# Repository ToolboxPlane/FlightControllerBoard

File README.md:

View this project on [CADLAB.io](https://cadlab.io/node/744). 

# FlightControllerBoard

A flight controller board for the mini Talon UAV based on a [STM32 Nucleo-32](http://www.st.com/content/st_com/en/products/evaluation-tools/product-evaluation-tools/mcu-eval-tools/stm32-mcu-eval-tools/stm32-mcu-nucleo/nucleo-l432kc.html).

Firmware availiable at [https://github.com/ToolboxBodensee/FlightController](https://github.com/ToolboxBodensee/FlightController).

## PCB

### Top layer

### Bottom Layer

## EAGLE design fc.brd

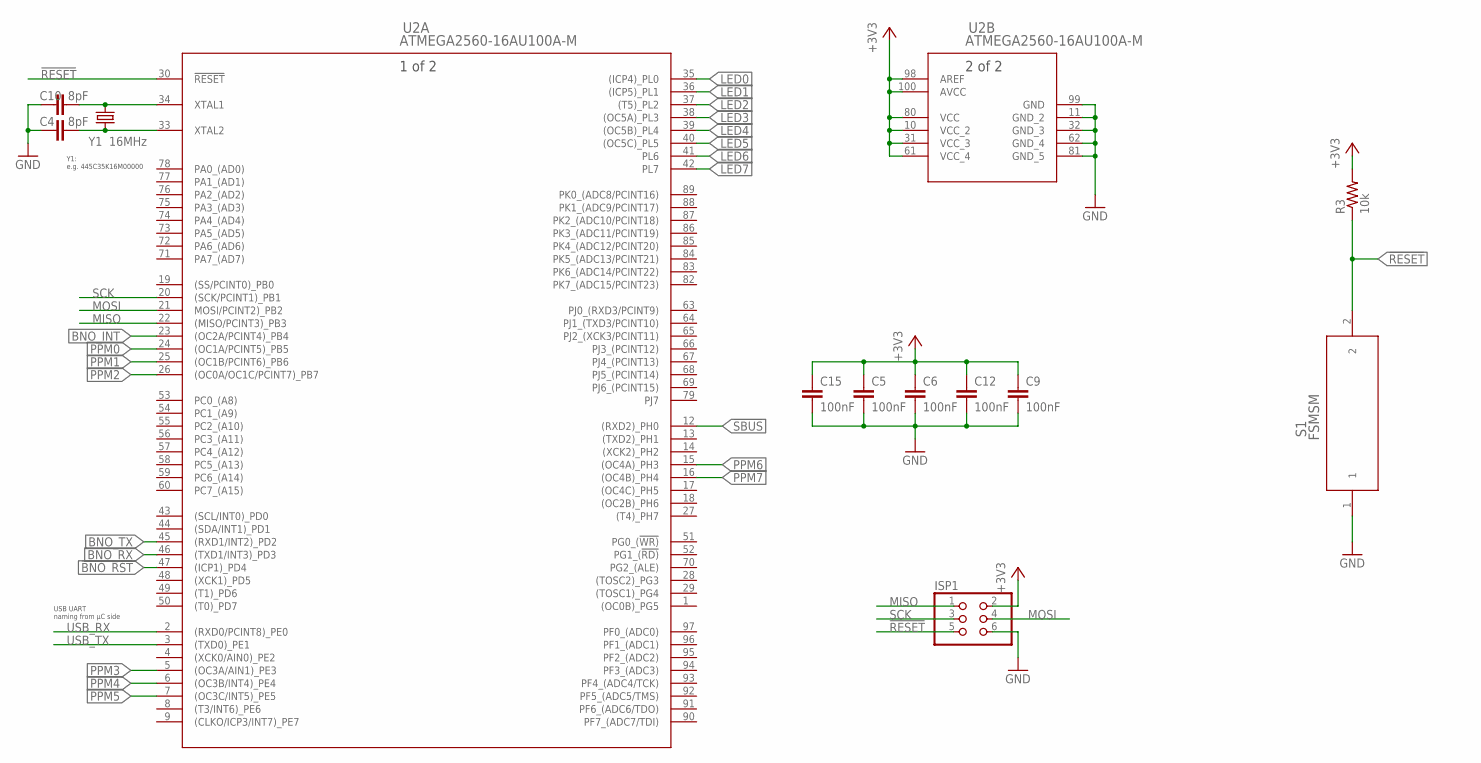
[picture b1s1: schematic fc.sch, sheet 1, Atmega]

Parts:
C4, C10: 8pF; 0603
C5, C6, C9, C12, C15: 100nF; 0603
ISP1: PINHD-2X3; 2X03
R3: 10k; 0603
S1: FSMSM; SWITCH_FSMSM
U2: ATMEGA2560-16AU100A-M; 100A-M
Y1: 16MHz; CRYSTAL-SMD-5X3.2-2PAD

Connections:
!BNO_RST: U2.47 ((ICP1)_PD4); also elsewhere on the board
!RESET: ISP1.5, R3.1, S1.2, U2.30 (!RESET)
!SBUS: U2.12 ((RXD2)_PH0); also elsewhere on the board
+3V3: C5.1, C6.1, C9.1, C12.1, C15.1, ISP1.2, R3.2, U2.10 (VCC_2), U2.31 (VCC_3), U2.61 (VCC_4), U2.80 (VCC), U2.98 (AREF), U2.100 (AVCC); also elsewhere on the board
BNO_INT: U2.23 ((OC2A/PCINT4)_PB4); also elsewhere on the board
BNO_RX: U2.46 ((TXD1/INT3)_PD3); also elsewhere on the board
BNO_TX: U2.45 ((RXD1/INT2)_PD2); also elsewhere on the board
GND: C4.1, C5.2, C6.2, C9.2, C10.1, C12.2, C15.2, ISP1.6, S1.1, U2.11 (GND_2), U2.32 (GND_3), U2.62 (GND_4), U2.81 (GND_5), U2.99 (GND); also elsewhere on the board
LED0: U2.35 ((ICP4)_PL0); also elsewhere on the board
LED1: U2.36 ((ICP5)_PL1); also elsewhere on the board
LED2: U2.37 ((T5)_PL2); also elsewhere on the board
LED3: U2.38 ((OC5A)_PL3); also elsewhere on the board
LED4: U2.39 ((OC5B)_PL4); also elsewhere on the board
LED5: U2.40 ((OC5C)_PL5); also elsewhere on the board
LED6: U2.41 (PL6); also elsewhere on the board
LED7: U2.42 (PL7); also elsewhere on the board
MISO: ISP1.1, U2.22 ((MISO/PCINT3)_PB3)
MOSI: ISP1.4, U2.21 (MOSI/PCINT2)_PB2)
unnamed: C10.2, U2.34 (XTAL1), Y1.P$2 (2)
unnamed: C4.2, U2.33 (XTAL2), Y1.P$1 (1)
PPM0: U2.24 ((OC1A/PCINT5)_PB5); also elsewhere on the board
PPM1: U2.25 ((OC1B/PCINT6)_PB6); also elsewhere on the board
PPM2: U2.26 ((OC0A/OC1C/PCINT7)_PB7); also elsewhere on the board
PPM3: U2.5 ((OC3A/AIN1)_PE3); also elsewhere on the board
PPM4: U2.6 ((OC3B/INT4)_PE4); also elsewhere on the board
PPM5: U2.7 ((OC3C/INT5)_PE5); also elsewhere on the board
PPM6: U2.15 ((OC4A)_PH3); also elsewhere on the board
PPM7: U2.16 ((OC4B)_PH4); also elsewhere on the board
SCK: ISP1.3, U2.20 ((SCK/PCINT1)_PB1)
USB_RX: U2.2 ((RXD0/PCINT8)_PE0); also elsewhere on the board
USB_TX: U2.3 ((TXD0)_PE1); also elsewhere on the board

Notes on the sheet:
Y1: e.g. 445C35K16M00000
USB UART naming from µC side

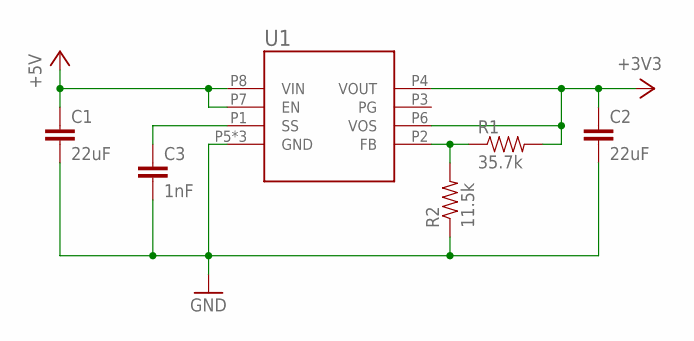
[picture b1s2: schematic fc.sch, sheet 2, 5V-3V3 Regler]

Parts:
C1, C2: 22uF; 0805
C3: 1nF; 0603
R1: 35.7k; 0603
R2: 11.5k; 0603
U1: LMZ21700; SIL0008E

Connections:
+3V3: C2.1, R1.2, U1.P4 (VOUT), U1.P6 (VOS); also elsewhere on the board
+5V: C1.1, U1.P7 (EN), U1.P8 (VIN); also elsewhere on the board
GND: C1.2, C2.2, C3.2, R2.1, U1.P5 (GND), U1.P9 (GND), U1.P10 (GND); also elsewhere on the board
unnamed: R1.1, R2.2, U1.P2 (FB)
unnamed: C3.1, U1.P1 (SS)

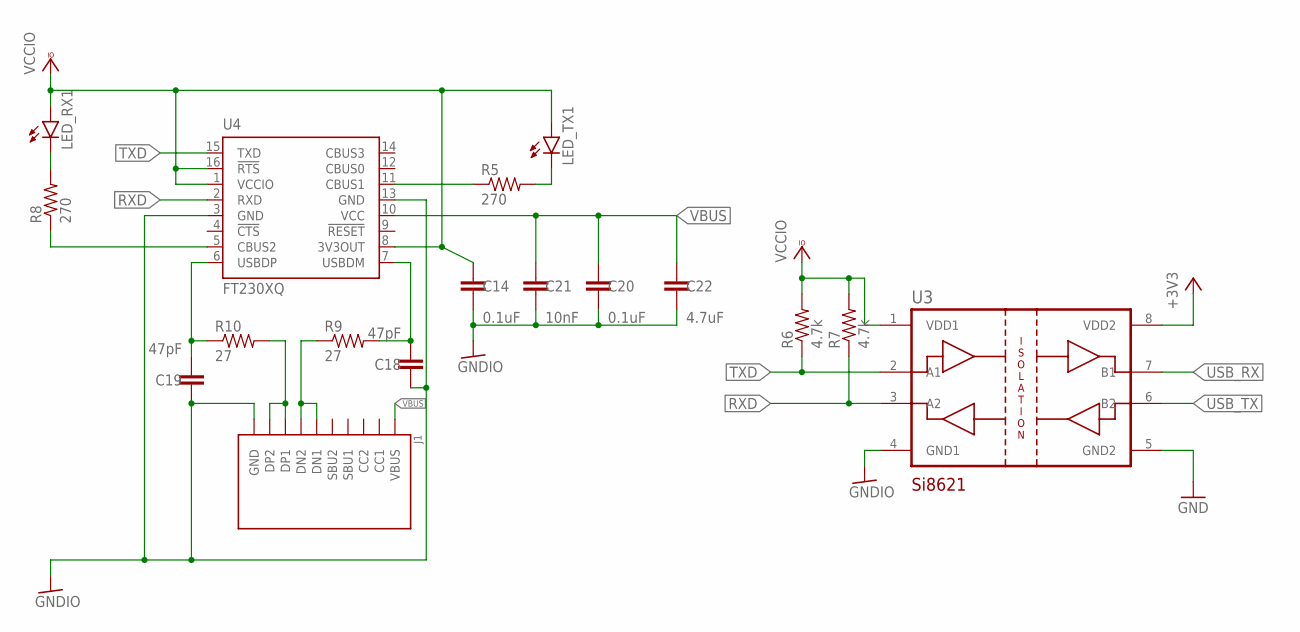
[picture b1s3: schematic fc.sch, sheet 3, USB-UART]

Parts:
C14, C20: 0.1uF; 0603
C18, C19: 47pF; 0603
C21: 10nF; 0603
C22: 4.7uF; 0603
J1: USBC
LED_RX1: LED0603; LED-0603
LED_TX1: LED0603; LED-0603
R5, R8: 270; 0603
R6, R7: 4.7k; 0603
R9, R10: 27; 0603
U3: SI8621AB-B-IS; SO08
U4: FT230XQ; QFN16

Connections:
+3V3: U3.8 (VDD2); also elsewhere on the board
D+1: J1.A6 (DP1), J1.B6 (DP2), R10.2
D-1: J1.A7 (DN1), J1.B7 (DN2), R9.1
GND: U3.5 (GND2); also elsewhere on the board
GNDIO: C14.2, C18.1, C19.1, C20.2, C21.2, C22.2, J1.A1 (GND), J1.A12 (GND), J1.S1 (GND), J1.S2 (GND), J1.S3 (GND), J1.S4 (GND), U3.4 (GND1), U4.3 (GND), U4.13 (GND)
unnamed: R5.1, U4.11 (CBUS1)
unnamed: LED_RX1.C, R8.2
unnamed: LED_TX1.C, R5.2
unnamed: R8.1, U4.5 (CBUS2)
RXD: R7.1, U3.3 (A2), U4.2 (RXD)
TXD: R6.1, U3.2 (A1), U4.15 (TXD)
USBDM1: C18.2, R9.2, U4.7 (USBDM)
USBDP1: C19.2, R10.1, U4.6 (USBDP)
USB_RX: U3.7 (B1); also elsewhere on the board
USB_TX: U3.6 (B2); also elsewhere on the board
VBUS: C20.1, C21.1, C22.1, J1.A4 (VBUS), J1.A9 (VBUS), U4.10 (VCC)
VCCIO: C14.1, LED_RX1.A, LED_TX1.A, R6.2, R7.2, U3.1 (VDD1), U4.1 (VCCIO), U4.8 (3V3OUT), U4.16 (!RTS)

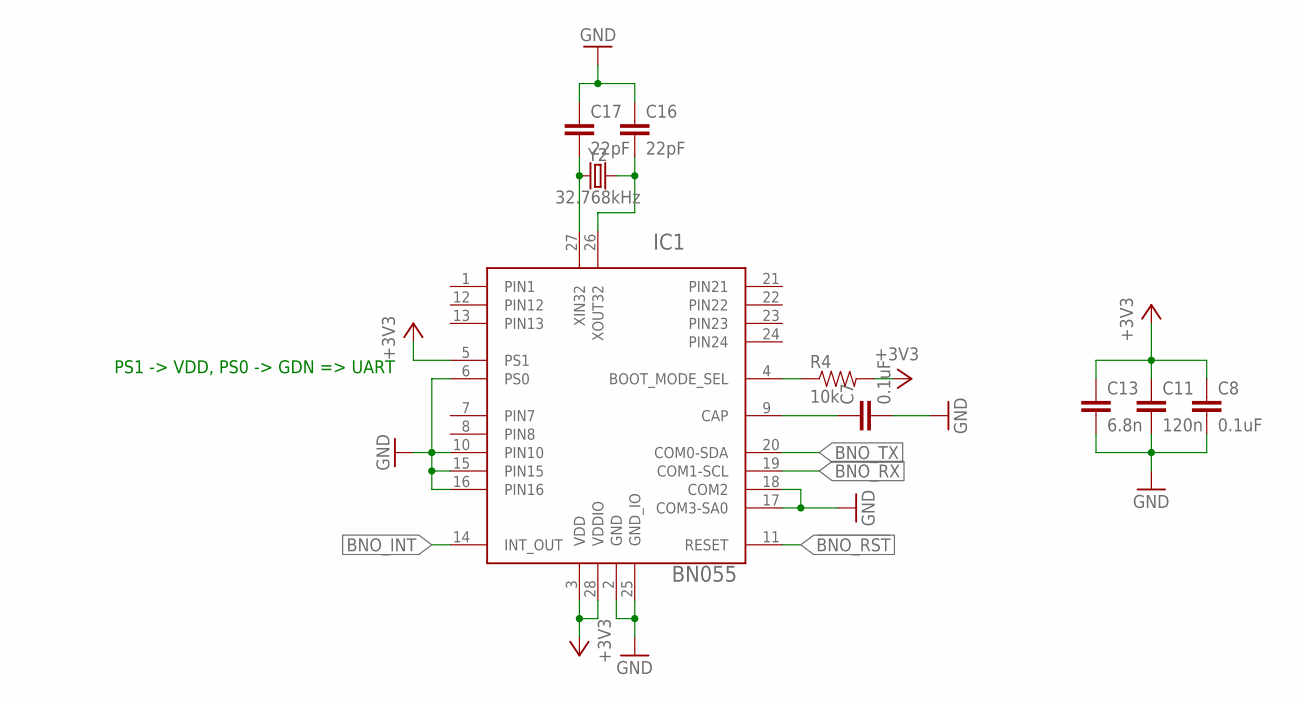
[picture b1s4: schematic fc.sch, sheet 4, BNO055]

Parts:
C7, C8: 0.1uF; 0603
C11: 120n; 0603
C13: 6.8n; 0603
C16, C17: 22pF; 0603
IC1: BN055; LGA-28_3.80X5.20/0.5
R4: 10k; 0603
Y2: 32.768kHz; CRYSTAL-SMD-3.2X1.5MM

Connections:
!BNO_RST: IC1.11 (RESET); also elsewhere on the board
+3V3: C8.1, C11.1, C13.1, IC1.3 (VDD), IC1.5 (PS1), IC1.28 (VDDIO), R4.2; also elsewhere on the board
BNO_INT: IC1.14 (INT_OUT); also elsewhere on the board
BNO_RX: IC1.19 (COM1-SCL); also elsewhere on the board
BNO_TX: IC1.20 (COM0-SDA); also elsewhere on the board
GND: C7.2, C8.2, C11.2, C13.2, C16.1, C17.1, IC1.2 (GND), IC1.6 (PS0), IC1.10 (PIN10), IC1.15 (PIN15), IC1.16 (PIN16), IC1.17 (COM3-SA0), IC1.18 (COM2), IC1.25 (GND_IO); also elsewhere on the board
unnamed: IC1.4 (BOOT_MODE_SEL), R4.1
unnamed: C7.1, IC1.9 (CAP)
unnamed: C17.2, IC1.27 (XIN32), Y2.P$1 (1)
unnamed: C16.2, IC1.26 (XOUT32), Y2.P$2 (2)

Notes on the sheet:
PS1 -> VDD, PS0 -> GDN => UART

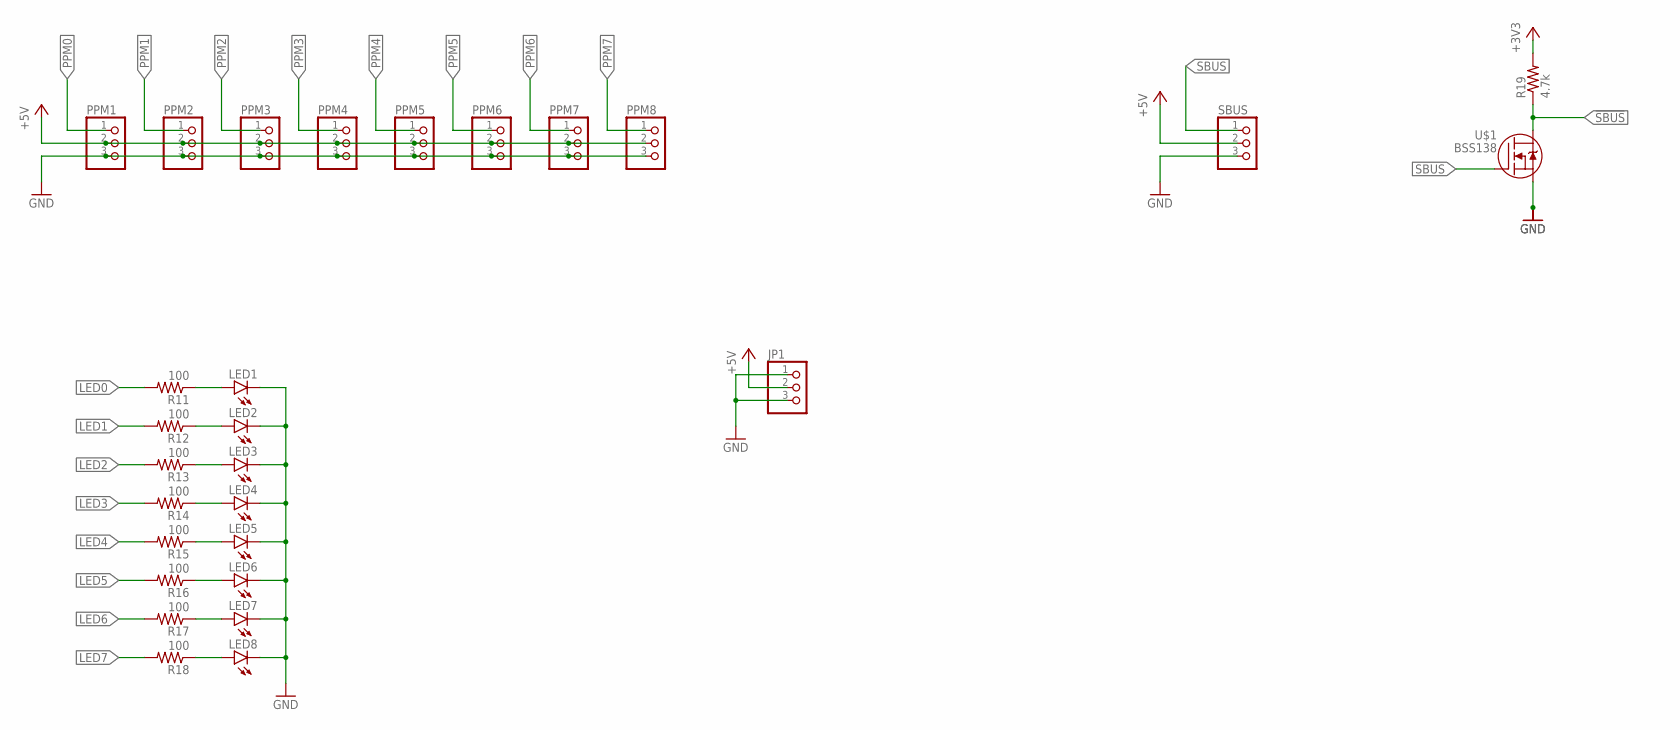
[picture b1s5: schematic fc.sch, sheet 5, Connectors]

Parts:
JP1: PINHD-1X3; 1X03
LED1, LED2, LED3, LED4, LED5, LED6, LED7, LED8: LED0603; LED-0603
PPM1, PPM2, PPM3, PPM4, PPM5, PPM6, PPM7, PPM8: PINHD-1X3; 1X03
R11, R12, R13, R14, R15, R16, R17, R18: 100; 0603
R19: 4.7k; 0603
SBUS: PINHD-1X3; 1X03
U$1: BSS138; SOT23

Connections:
!SBUS: R19.1, U$1.3 (D); also elsewhere on the board
+3V3: R19.2; also elsewhere on the board
+5V: JP1.2, PPM1.2, PPM2.2, PPM3.2, PPM4.2, PPM5.2, PPM6.2, PPM7.2, PPM8.2, SBUS.2; also elsewhere on the board
GND: JP1.1, JP1.3, LED1.C, LED2.C, LED3.C, LED4.C, LED5.C, LED6.C, LED7.C, LED8.C, PPM1.3, PPM2.3, PPM3.3, PPM4.3, PPM5.3, PPM6.3, PPM7.3, PPM8.3, SBUS.3, U$1.2 (S); also elsewhere on the board
LED0: R11.2; also elsewhere on the board
LED1: R12.2; also elsewhere on the board
LED2: R13.2; also elsewhere on the board
LED3: R14.2; also elsewhere on the board
LED4: R15.2; also elsewhere on the board
LED5: R16.2; also elsewhere on the board
LED6: R17.2; also elsewhere on the board
LED7: R18.2; also elsewhere on the board
unnamed: LED2.A, R12.1
unnamed: LED3.A, R13.1
unnamed: LED4.A, R14.1
unnamed: LED5.A, R15.1
unnamed: LED6.A, R16.1
unnamed: LED7.A, R17.1
unnamed: LED8.A, R18.1
unnamed: LED1.A, R11.1
PPM0: PPM1.1; also elsewhere on the board
PPM1: PPM2.1; also elsewhere on the board
PPM2: PPM3.1; also elsewhere on the board
PPM3: PPM4.1; also elsewhere on the board
PPM4: PPM5.1; also elsewhere on the board
PPM5: PPM6.1; also elsewhere on the board
PPM6: PPM7.1; also elsewhere on the board
PPM7: PPM8.1; also elsewhere on the board
SBUS: SBUS.1, U$1.1 (G)

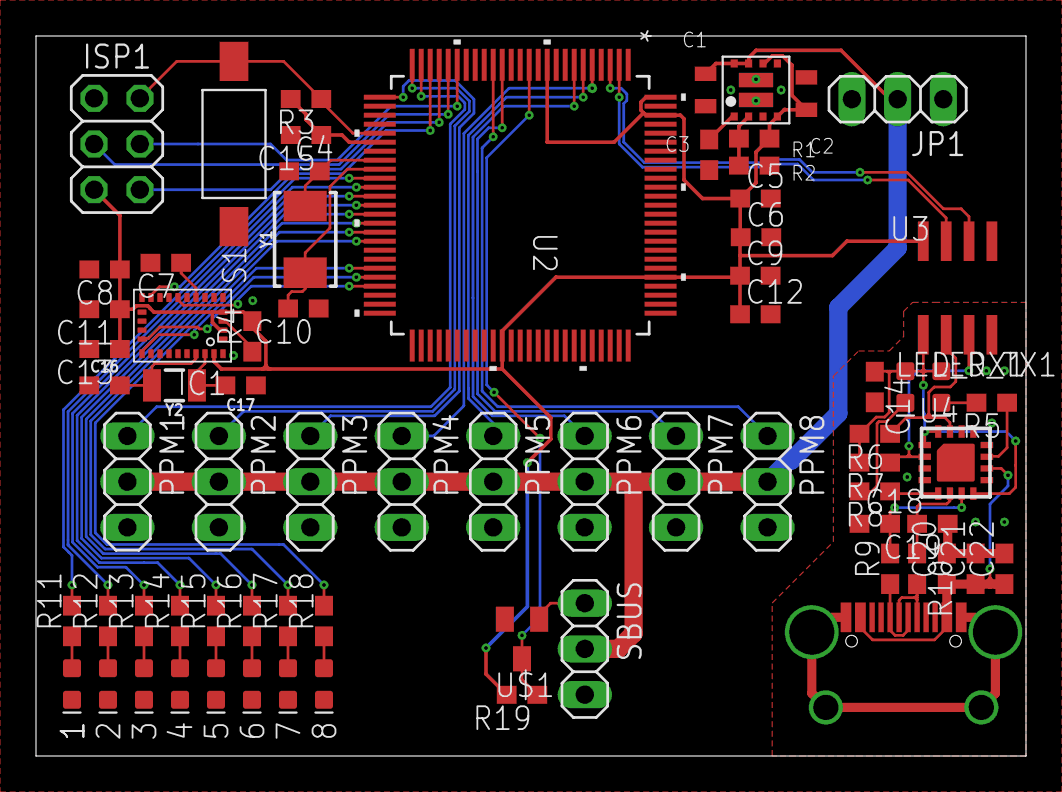
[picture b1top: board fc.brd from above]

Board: 2 copper layers, 55.0 x 40.0 mm, 72 parts (0 on the bottom side), 60 nets.

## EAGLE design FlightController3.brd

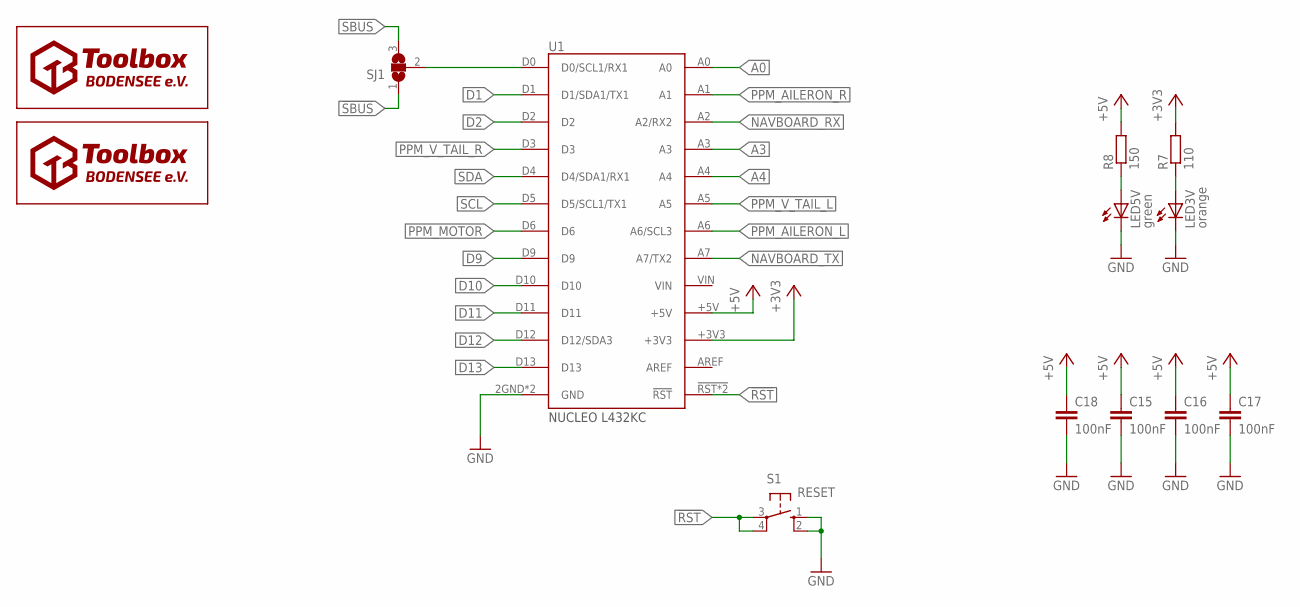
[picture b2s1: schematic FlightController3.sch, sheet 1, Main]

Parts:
C15, C16, C17, C18: 100nF; C1206
LED3V: orange; SML0603
LED5V: green; SML0603
R7: 110; R0603
R8: 150; R0603
S1: RESET; B3F-10XX
SJ1: SJ2W; SJ_2
U1: NUCLEO_L432KC; NUCLEO
U$1, U$2: TOOLBOX_LOGO; TOOLBOX

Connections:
!RST: S1.3, S1.4 (P1), U1.2!RST (!RST), U1.!RST; also elsewhere on the board
!SBUS: SJ1.1; also elsewhere on the board
+3V3: R7.2, U1.+3V3; also elsewhere on the board
+5V: C15.1, C16.1, C17.1, C18.1, R8.2, U1.+5V; also elsewhere on the board
A0: U1.A0; also elsewhere on the board
A3: U1.A3; also elsewhere on the board
A4: U1.A4; also elsewhere on the board
D1: U1.D1 (D1/SDA1/TX1); also elsewhere on the board
D2: U1.D2; also elsewhere on the board
D9: U1.D9; also elsewhere on the board
D10: U1.D10; also elsewhere on the board
D11: U1.D11; also elsewhere on the board
D12: U1.D12 (D12/SDA3); also elsewhere on the board
D13: U1.D13; also elsewhere on the board
GND: C15.2, C16.2, C17.2, C18.2, LED3V.C, LED5V.C, S1.1 (S), S1.2 (S1), U1.2GND (GND), U1.GND; also elsewhere on the board
unnamed: LED3V.A, R7.1
unnamed: LED5V.A, R8.1
unnamed: SJ1.2, U1.D0 (D0/SCL1/RX1)
NAVBOARD_RX: U1.A2 (A2/RX2); also elsewhere on the board
NAVBOARD_TX: U1.A7 (A7/TX2); also elsewhere on the board
PPM_AILERON_L: U1.A6 (A6/SCL3); also elsewhere on the board
PPM_AILERON_R: U1.A1; also elsewhere on the board
PPM_MOTOR: U1.D6; also elsewhere on the board
PPM_V_TAIL_L: U1.A5; also elsewhere on the board
PPM_V_TAIL_R: U1.D3; also elsewhere on the board
SBUS: SJ1.3; also elsewhere on the board
SCL: U1.D5 (D5/SCL1/TX1); also elsewhere on the board
SDA: U1.D4 (D4/SDA1/RX1); also elsewhere on the board
VIN: U1.VIN

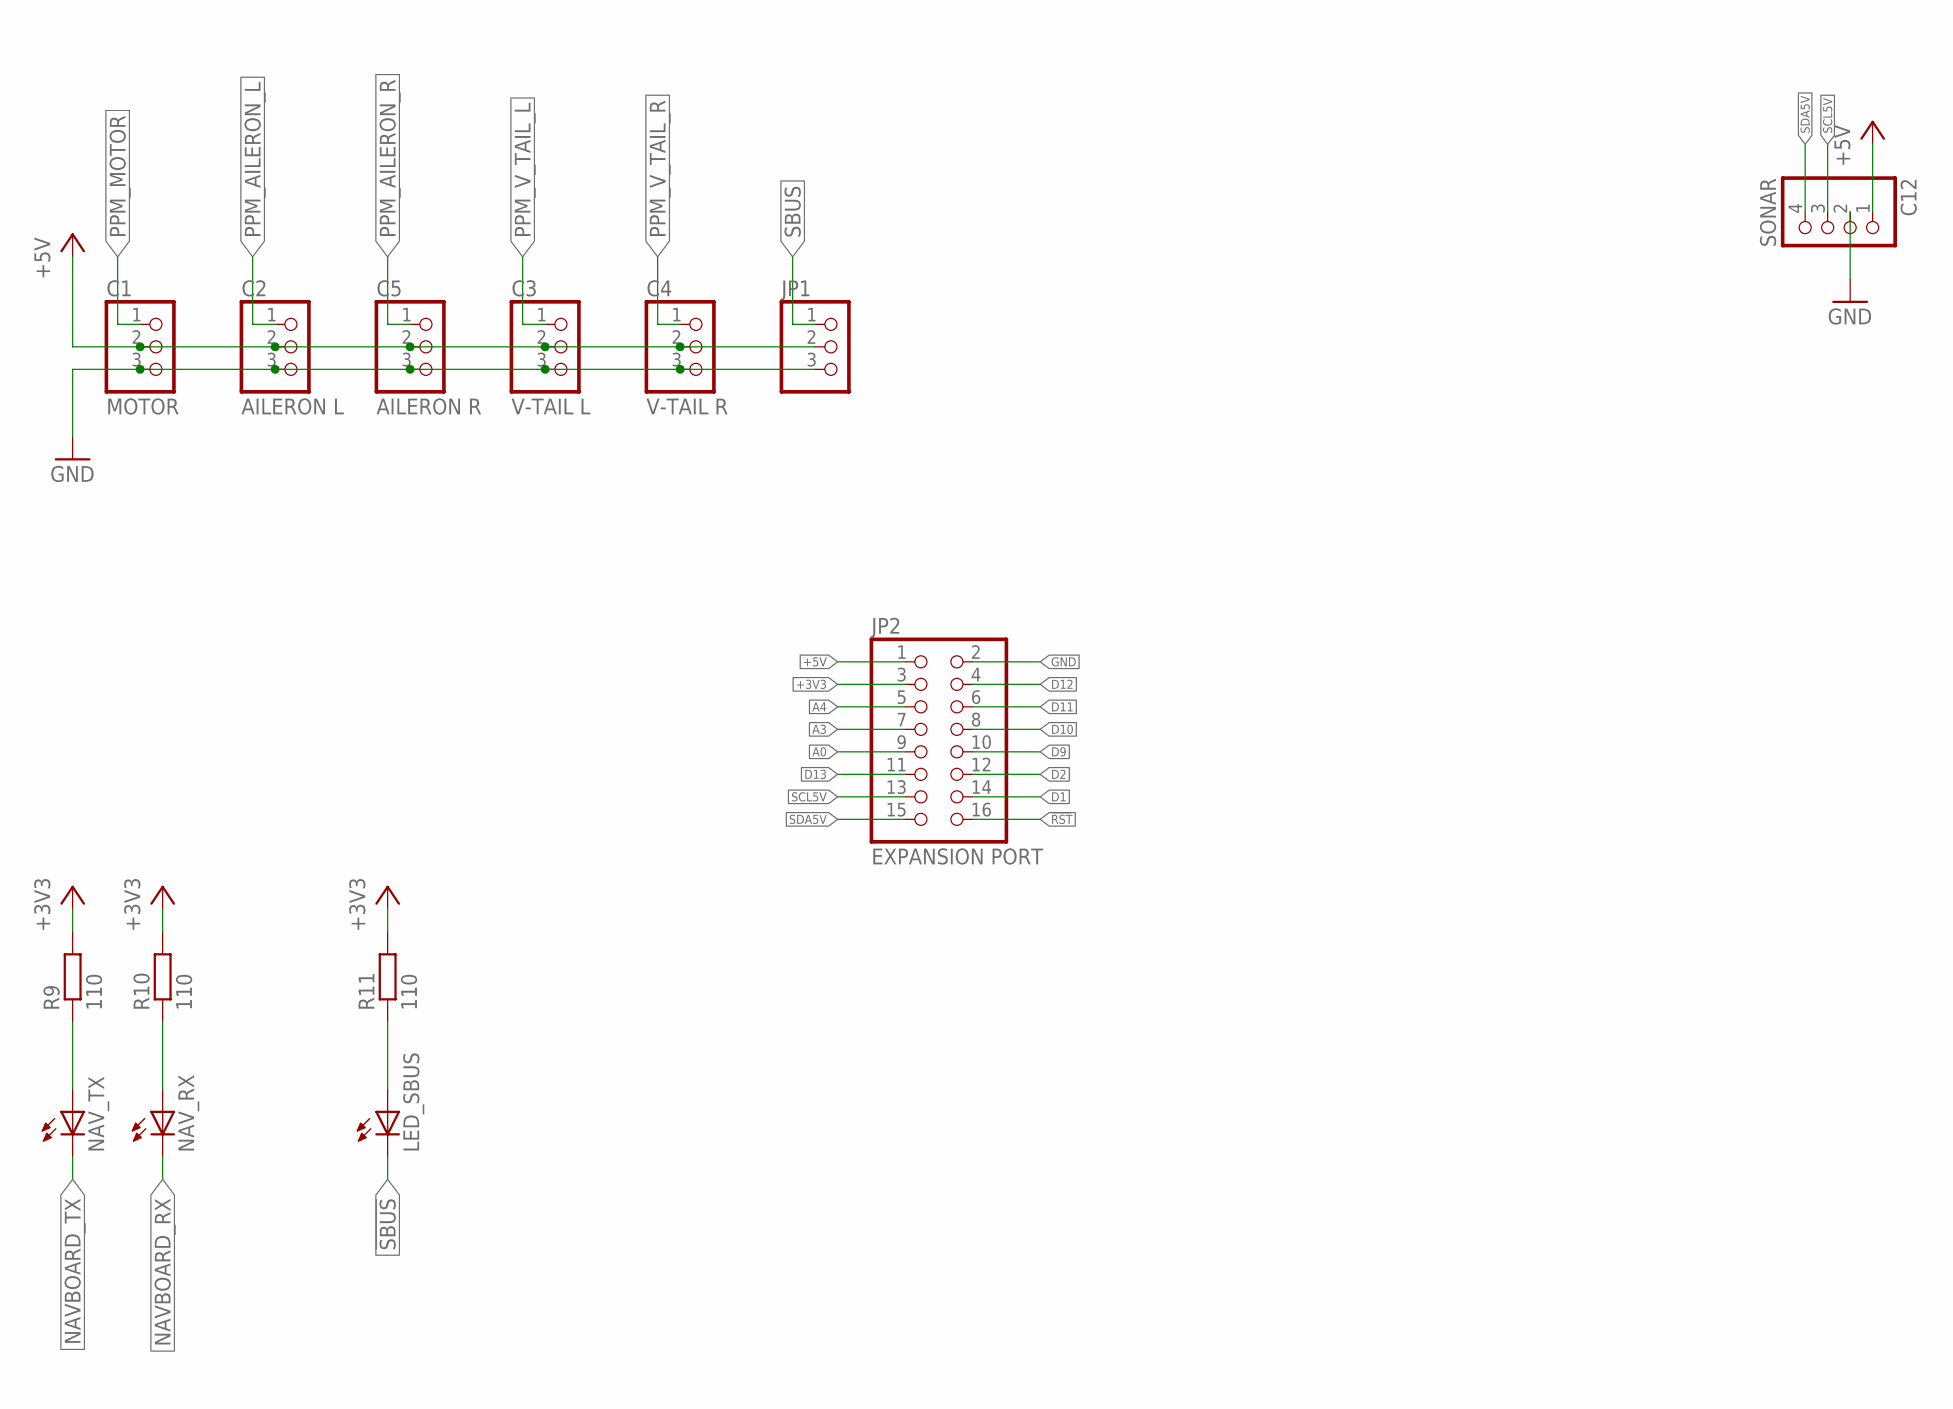
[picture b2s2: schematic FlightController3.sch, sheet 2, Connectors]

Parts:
C1: MOTOR; 1X03
C2: AILERON L; 1X03
C3: V-TAIL L; 1X03
C4: V-TAIL R; 1X03
C5: AILERON R; 1X03
C12: SONAR; 1X04
JP1: PINHD-1X3; 1X03
JP2: EXPANSION PORT; 2X08
LED_SBUS: LEDSML0603; SML0603
NAV_RX: LEDSML0603; SML0603
NAV_TX: LEDSML0603; SML0603
R9, R10, R11: 110; R0603

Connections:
!RST: JP2.16; also elsewhere on the board
!SBUS: LED_SBUS.C; also elsewhere on the board
+3V3: JP2.3, R9.2, R10.2, R11.2; also elsewhere on the board
+5V: C1.2, C2.2, C3.2, C4.2, C5.2, C12.1, JP1.2, JP2.1; also elsewhere on the board
A0: JP2.9; also elsewhere on the board
A3: JP2.7; also elsewhere on the board
A4: JP2.5; also elsewhere on the board
D1: JP2.14; also elsewhere on the board
D2: JP2.12; also elsewhere on the board
D9: JP2.10; also elsewhere on the board
D10: JP2.8; also elsewhere on the board
D11: JP2.6; also elsewhere on the board
D12: JP2.4; also elsewhere on the board
D13: JP2.11; also elsewhere on the board
GND: C1.3, C2.3, C3.3, C4.3, C5.3, C12.2, JP1.3, JP2.2; also elsewhere on the board
unnamed: NAV_TX.A, R9.1
unnamed: NAV_RX.A, R10.1
unnamed: LED_SBUS.A, R11.1
NAVBOARD_RX: NAV_RX.C; also elsewhere on the board
NAVBOARD_TX: NAV_TX.C; also elsewhere on the board
PPM_AILERON_L: C2.1; also elsewhere on the board
PPM_AILERON_R: C5.1; also elsewhere on the board
PPM_MOTOR: C1.1; also elsewhere on the board
PPM_V_TAIL_L: C3.1; also elsewhere on the board
PPM_V_TAIL_R: C4.1; also elsewhere on the board
SBUS: JP1.1; also elsewhere on the board
SCL5V: C12.3, JP2.13; also elsewhere on the board
SDA5V: C12.4, JP2.15; also elsewhere on the board

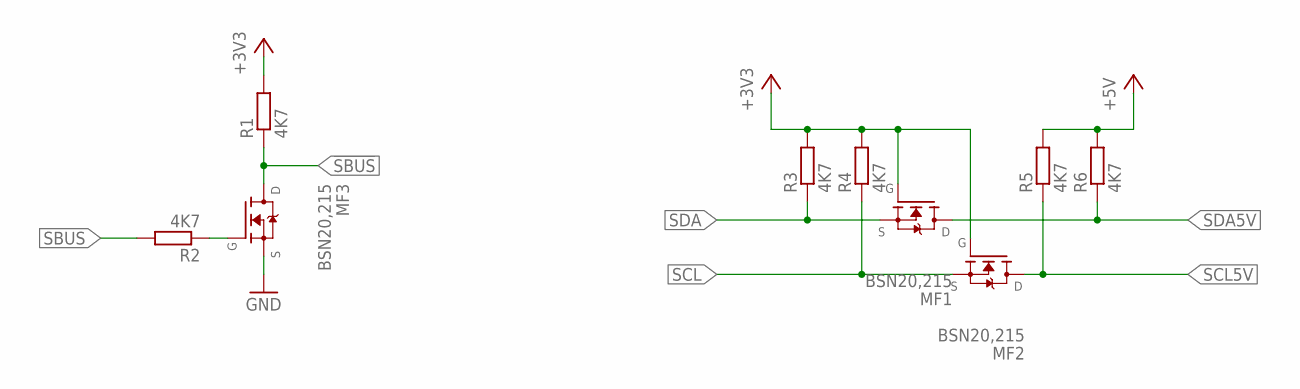
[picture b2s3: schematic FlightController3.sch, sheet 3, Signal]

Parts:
MF1, MF2, MF3: BSN20,215; BSN20_215
R1, R2, R3, R4, R5, R6: 4K7; R0603

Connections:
!SBUS: MF3.3 (D), R1.1; also elsewhere on the board
+3V3: MF1.1 (G), MF2.1 (G), R1.2, R3.2, R4.2; also elsewhere on the board
+5V: R5.2, R6.2; also elsewhere on the board
GND: MF3.2 (S); also elsewhere on the board
unnamed: MF3.1 (G), R2.1
SBUS: R2.2; also elsewhere on the board
SCL: MF2.2 (S), R4.1; also elsewhere on the board
SCL5V: MF2.3 (D), R5.1; also elsewhere on the board
SDA: MF1.2 (S), R3.1; also elsewhere on the board
SDA5V: MF1.3 (D), R6.1; also elsewhere on the board

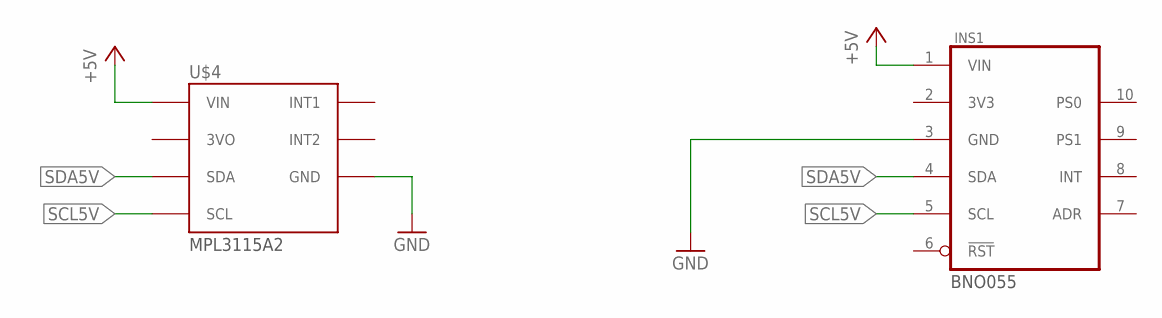
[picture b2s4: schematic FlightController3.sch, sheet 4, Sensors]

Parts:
INS1: BNO055; BNO055-BREAKOUT
U$4: MPL3115A2

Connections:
+5V: INS1.1 (VIN), U$4.VIN; also elsewhere on the board
GND: INS1.3 (GND), U$4.GND; also elsewhere on the board
SCL5V: INS1.5 (SCL), U$4.SCL; also elsewhere on the board
SDA5V: INS1.4 (SDA), U$4.SDA; also elsewhere on the board

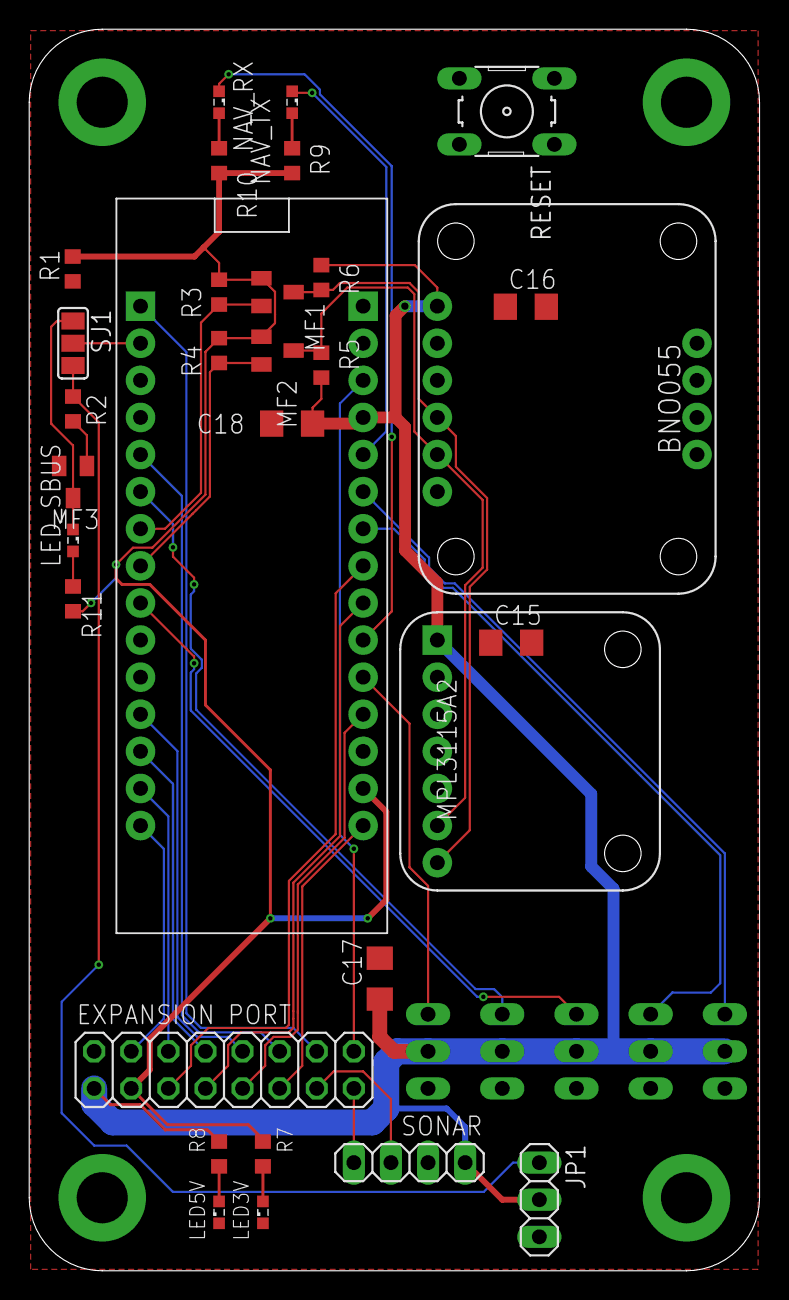
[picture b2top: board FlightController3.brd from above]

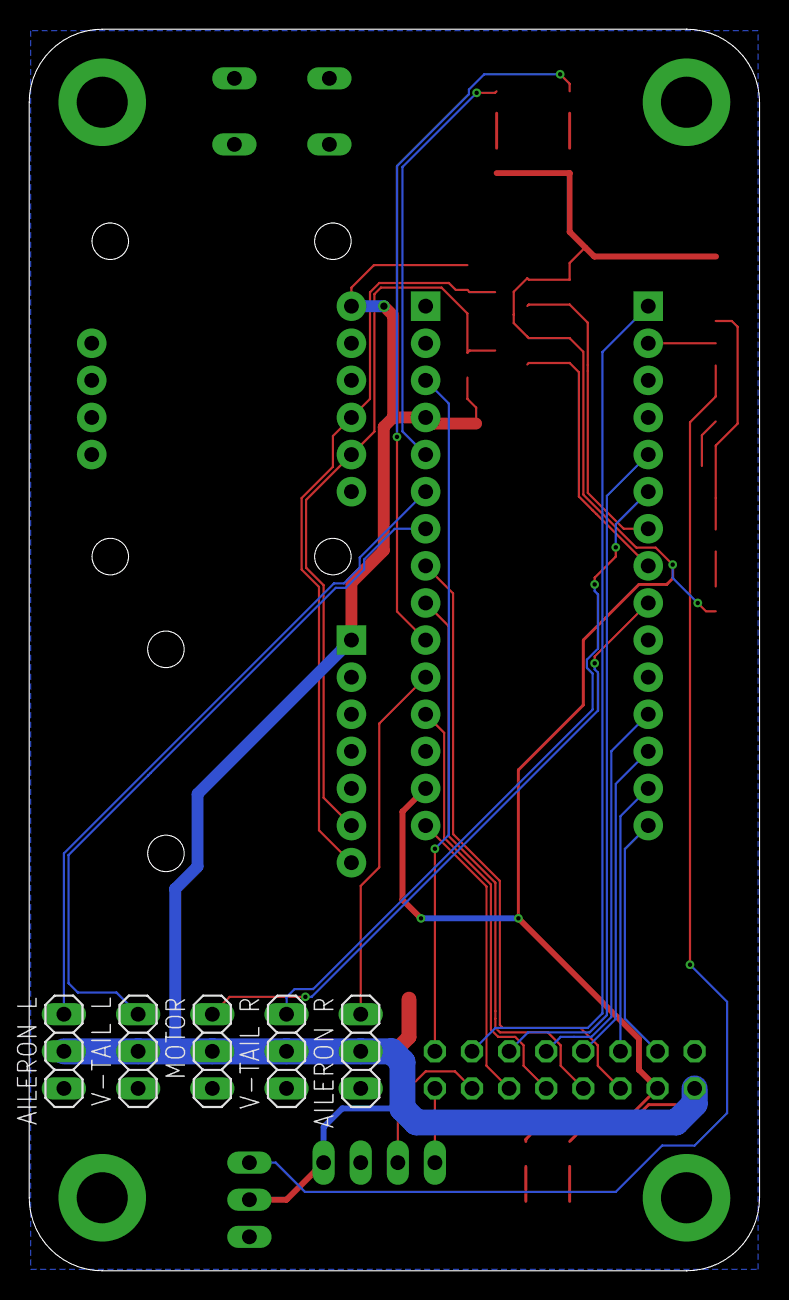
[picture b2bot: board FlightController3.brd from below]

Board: 2 copper layers, 50.0 x 85.0 mm, 38 parts (5 on the bottom side), 34 nets.

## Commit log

2017-04-17 Sonar, I2C Expansion Ports, Logo, Various Improvements
2017-04-18 preview images for documentation
2017-04-18 Update README.md
    added images to readme
2017-04-18 changed version to 8.1.1
2017-04-18 fixed toolbox logo
2017-04-18 added reset header
2017-04-18 added mounting holes, removed BNO-055 mounting holes
2017-04-20 power LEDs
2017-04-20 capacitors, dimensions, reset button
2017-04-20 various improvements, mostly silkscreen labels
2017-04-21 fixed naming of D1/D0 and SBUS connection
2017-04-21 removed GPIO, I2C Ports, added expansion port
2017-04-21 smaller board footprint, added reset to port
2017-04-21 rounded edges
2017-04-22 Added SBUS, I²C and UART LEDs
2017-04-22 Removed Eagle Files
2017-04-23 Fixed several issues
2017-04-23 Added more files to gitignore
2017-05-11 jumper to select between SBUS and !SBUS
2017-05-11 eeprom and stuff
2017-05-13 various fixes
2017-10-20 updated gitignore to include gerber files
    Source: https://github.com/github/gitignore/blob/master/Eagle.gitignore
2017-10-22 eagle 8.4.0
2017-10-23 sbus inverter spice setup
2017-10-23 i2c level shifting simulation setup
2017-10-23 power led simulation setup
2017-10-23 filtering capacitor simulation setup
2017-10-23 nucleo simulation setup
2017-10-23 EEPROM simulation setup
2017-10-23 signal LED simulation setup
2018-03-09 Backlink to CADLAB.io has been added.
2018-10-20 Started FC4
2018-10-20 First draft of the schematic finished
2018-10-20 Initial draft for the layout
2018-10-21 Small changes, added reset button
2018-10-30 Improved the design
2018-11-05 Spannungsregler
2018-11-05 FTDI hauptsächlich
2018-11-05 LED alignment
2018-12-02 cleanup
    airwire in pad/alignment
2018-12-02 led placement on grid
2018-12-02 connected LEDs
2018-12-02 led labels
2018-12-02 aligned atmega breakout vias
2018-12-02 atmega breakout cleanup
2018-12-02 isp, reset button, gnd polygon
2018-12-02 reset, alignment, caps
    reset button
    aligned sbus inverter to grid
    moved decoupling cap to sensible position
2018-12-02 minor changes to usb layout
2018-12-02 changed caps to sparkfun lib
2018-12-02 changed LEDs to sparkfun lib
2018-12-02 changed resistors to sparkfun lib
    how nice, all the 0603 parts are the same size now.
2018-12-02 move led resistors up
2018-12-02 fixed obviously wrong DRC errors
    (?)
2019-04-03 And Now for Something Completely Different
2019-04-03 LMZM23600 from official kicad lib
2019-04-03 add gitignore
2019-04-03 remove temporary file
    (added by accident)
2019-04-03 add fp-info-cache to gitignore
2019-04-03 update PCB to match schematic changes
2019-04-04 use submodule for FT230
2019-04-04 pullups, jumpers
2019-04-05 LED, Mounting Holes
    LEDs to register L
    Mounting Holes
    XT30
2019-04-06 layout
2019-04-06 fix Y1 connection
2019-04-06 small layout fixes
2019-04-07 silkscreen logos
2019-04-07 rebuild zones
2019-04-07 fix power input
2019-04-07 optimize gnd connections
2019-04-07 added NCs to satisfy ERC
2019-04-27 fix LED resistor values

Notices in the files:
parts and their libraries:
SparkFun-Clocks: Licensing: Creative Commons ShareAlike 4.0 International - https://creativecommons.org/licenses/by-sa/4.0
